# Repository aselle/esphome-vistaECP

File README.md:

# Honeywell/Ademco Vista ECP ESPHome custom component and library

## This fork provides a PCB

This is based on work that was discussed on the main fork issues at 
https://github.com/Dilbert66/esphome-vistaECP/issues/49

Based on the work of the main fork, I created a design and pcb. At the time, the main fork did not provide a fully isolated schematic, which I wanted if I was going to use this on my system.  I invetsigated several designs and settled on this one for my uses. The issue describes a lot of the possibilites. In the end, I used 3 optocouplers and 2 transistors.
You should be able to get the board manufactured cheaply e.g. on JLCPCB.

This is provided with no warranty implied or explicit. I can not be held responsible for you using this work. While, I have tested this in my own equipment for over a year, I suspect the main fork is better tested, so I would recommend this approach only for advanced users who know how to use an oscilloscope.
 
* circuit/v1-manufacture-files
  * has gerber, pdf schematic and case stl files
* circuit/kicad
  * KiCad source for the pcb.

Here's the isolated schematic

Here is what the manufactured product looks like

## Main fork documentation

This is an implementation of an ESPHOME custom component and ESP Library to interface directly to a Safewatch/Honeywell/Ademco Vista 15/20 alarm system using the ECP interface and very inexpensive ESP8266/ESP32 modules .  The ECP library code is based on the arduino source code from Mark Kimsal's repository located at  https://github.com/TANC-security/keypad-firmware.  It has been  completely rewritten as a class and adapted to work on the ESP8266/ESP32 platform using interrupt driven communications and pulse timing. A custom modified version of Peter Lerup's ESPsoftwareserial library (https://github.com/plerup/espsoftwareserial) was also used for the serial communications to work more efficiently within the tight timing of the ESP8266 interrupt window. 

To compensate for the limitations of the minimal zone data sent by the panel, a time to live (TTL) attribute for each faulted zone was used.  The panel only sends fault messages when a zone is faulted or alarmed and does not send data when the zone is restored, therefore the TTL timer is used to reset a zone after a preset duration once it stops receiving those fault/alarm messages for that zone.  You can tweak the TTL setting in the YAML.  The default timer is set to 30 seconds.  I've also added persistent storage and recovery for zone status in the event of a power failure or reboot of the ESP.  The system will use persistent storage to recover the last known status of the zone on restart.

From documented info, it seems that some panels send an F2 command with extra system details but the panel I have here (Vista 20P version 3.xx ADT version) does not.  Only the F7 is available for zone and system status in my case but this is good enough for this purpose. 

As far as writing on the bus and the request to send pulsing sequence, most documentation only discusses keypad traffic and this only uses the the 3rd pulse.  In actuality the pulses are used as noted below depending on the device type requesting to send:
```
Panel pulse 1. Addresses 1-7, expander board (07), etc
Panel pulse 2. Addresses 8-15 - zone expanders, relay modules
Panel pulse 3. Addresses 16-23 - keypads
```
For example, a zone expander that has the address 07, will send it's address on the first pulse only and will send nothing for the 2nd and 3rd pulse.  A keypad with address 16, will send a 1 bit pulse for pulse1 and pulse2 and then it's encoded address on pulse 3. This info was determined from analysis using a zone expander board and Pulseview to monitor the bus. 

If you are not familiar with ESPHome , I suggest you read up on this application at https://esphome.io and home assistant at https://www.home-assistant.io/.   The library class itself can be used outside of the esphome and home assistant systems.  Just use the code as is without the vistalalarm.yaml and vistaalarm.h files and call it's functions within your own application.  

To use this software you simply place the vistaAlarm.yaml file in your main esphome directory, then copy the *.h and *.cpp files from the vistaEcpInterface directory to a similarly named subdirectory (case sensitive) in your esphome main directory and then compile the yaml as usual. The directory name is in the "includes:" option of the yaml.

##### Notes: 
* If you use the zone expanders and/or LRR functions, you might need to clear CHECK messages for the LRR and expanded zones from the panel on boot or restart by entering your access code followed by 1 twice. eg 12341 12341 where 1234 is your access code.

The yaml attributes should be fairly self explanatory for customization. The yaml example also shows how to setup named zones. 

## Features:

* Full zone expander emulation (4219/4229) which will give you  an additional 8 zones to the system per emulated expander plus associated relay outputs. Currently the library will provide emulation for 2 boards for a total of 16 additionals zones. You can even use free pins on the chip as triggers for those zones as well. 

* Relay module emulation. (4204). The system can support 4 module addresses for a total of 16 relay channels. 

* Long Range Radio (LRR) emulation (or monitoring) statuses for more detailed status messages

* Zone status - Open, Busy, Alarmed and Closed with named zones

* Arm, disarm or send any sequence of commands to the panel

* Status indicators - fire, alarm, trouble, armed stay, armed away, instant armed, armed night,  ready, AC status, bypass status, chime status,battery status, check status, zone and relay channel status fields.

* Optional ability to monitor other devices on the bus such as keypads, other expanders, relay boards, RF devices, etc. This requires the #define MONITORTX to be uncommented in vista.h as well as the addition of two resistors (R4 and R5) to the circuit as shown in the schematic.   This adds another serial interrupt routine that captures and decodes all data on the green tx line.  If enabled this data will be used to update zone statuses for external modules.

The following services are published to home assistant for use in various scripts. 

	alarm_disarm: Disarms the alarm with the user code provided, or the code specified in the configuration.
	alarm_arm_home: Arms the alarm in home mode.
	alarm_arm_away: Arms the alarm in away mode.
	alarm_arm_night: Arms the alarm in night mode (no entry delay).
	alarm_trigger_panic: Trigger a panic alarm.
        alarm_trigger_fire: Trigger a fire alarm.
	alarm_keypress: Sends a string of characters to the alarm system. 

## Example in Home Assistant

The returned statuses for Home Assistant are: armed_away, armed_home, armed_night, pending, disarmed,triggered and unavailable.  

Sample Home Assistant Template Alarm Control Panel configuration with simple services (defaults to partition 1):

```
alarm_control_panel:
  - platform: template
    panels:
      safe_alarm_panel:
        name: "Alarm Panel"
        value_template: "{{states('sensor.vistaalarm_system_status')}}"
        code_arm_required: false
        
        arm_away:
          - service: esphome.vistaalarm_alarm_arm_away
                  
        arm_home:
          - service: esphome.vistaalarm_alarm_arm_home
          
        arm_night:
          - service: esphome.vistaalarm_alarm_arm_night
            data_template:
              code: '{{code}}' #if you didnt set it in the yaml, then send the code herefschema
          
        disarm:
          - service: esphome.vistaalarm_alarm_disarm
            data_template:
              code: '{{code}}'                    
```

## Services

- Basic alarm services. These services default to partition 1:

	- "alarm_disarm", Parameter: "code" (access code)
	- "alarm_arm_home" 
	- "alarm_arm_night", Parameter: "code" (access code)
	- "alarm_arm_away"
	- "alarm_trigger_panic"
	- "alarm_trigger_fire"

- Intermediate command service. Use this service if you need more versatility such as setting alarm states on any partition:

	- "set_alarm_state",  Parameters: "partition","state","code"  where partition is the partition number from 1 to 8, state is one of "D" (disarm), "A" (arm_away), "S" (arm_home), "N" (arm_night), "P" (panic) or "F" (fire) and "code" is your panel access code (can be empty for arming, panic and fire cmds )

- Generic command service. Use this service for more complex control:

	- "alarm_keypress",  Parameter: "keys" where keys can be any sequence of keys accepted by your panel. For example to arm in night mode you set keys to be "xxxx33" where xxxx is your access code. 
    
    - "set_zone_fault",Parameters: "zone","fault" where zone is a zone from 9 - 48 and fault is 0 or 1 (0=ok, 1=open)
       The zone number will depend on what your expander address is set to.

## Wiring

### Non-isolated simple version

### Alternative version using transistors instead of an optocoupler for transmit

### Ground Isolated version

## Wiring Notes

* Optocouplers should have a minimum CTR of 50. Recommendations are the 4N35 or TLP521. You can vary the resistor values for the simple version but keep the ratio similar for the voltage dividers R2/R3 and R4/R5. R1 should not be set below 150 ohm. Resistor values are chosen to minimize load on ECP bus while still providing full output signals on the optocouplers. 
* My goal was to keep the design as simple as possible without causing any bus load or interference with maximum signal fidelity.  Since the transmit circuit required high side switching I opted to use an optocoupler since I had a few on hand and it simplified the amount of components needed but proved to have it's own issues as far as CTR requirements.  For those that would prefer not using optocouplers due to availability or other reasons, i've provided a version using transistors for the transmit circuit instead.  

## OTA updates
In order to make OTA updates, connection switch in frontend should be switched to OFF since the  ECP library is using interrupts.

## MQTT with HomeAssistant
If your preference is to use MQTT instead of ESPHOME, you can use the Arduino sketch from the MQTT-Example directory. It supports pretty much all functions of the ESPHOME implementation.  To use, edit the configuration items at the top of the file for your setup then simply put the ino and all *.h and *.cpp vista library files (from directory /src/vistaEcpInterface) in the same sketch directory and compile.  Read the comments within the sketch for more details.   The sketch also supports ArduinoOTA (https://www.arduino.cc/reference/en/libraries/arduinoota/) that will enable you to update the code via wifi once the initial upload is done.  

## Custom Alarm Panel Card

I've added a sample lovelace alarm-panel card copied from the repository at https://github.com/GalaxyGateway/HA-Cards. I've customized it to work with this ESP library's services.   I've also added two new text fields that will be used by the card to display the panel prompts the same way a real keypad does. To configure the card, just place the alarm-panel-card.js file into the /config/www directory of your homeassistant installation and add a new resource in your lovelace configuration pointing to /local/alarm-panel-card.js.  You can then configure the card as shown below. Just substitute your service name to your application.

```
type: 'custom:alarm-keypad-card'
title: Vista_ESPHOME
unique_id: vista1
disp_line1: sensor.vistaalarm_line1
disp_line2: sensor.vistaalarm_line2
scale: 1
service_type: esphome
service: vistaalarm_alarm_keypress
status_A: AWAY
status_B: STAY
status_C: READY
status_D: BYPASS
status_E: TROUBLE
status_F: ''
status_G: ''
status_H: ''
sensor_A: binary_sensor.vistaalarm_away
sensor_B: binary_sensor.vistaalarm_stay
sensor_C: binary_sensor.vistaalarm_ready
sensor_D: binary_sensor.vistaalarm_bypass
sensor_E: binary_sensor.vistaalarm_trouble
button_A: STAY
button_B: AWAY
button_C: DISARM
button_D: BYPASS
button_F: <
button_G: '>'
button_E: ' '
button_H: ' '
cmd_A:
  keys: '12343'
cmd_B:
  keys: '12342'
cmd_C:
  keys: '12341'
cmd_D:
  keys: '12346#'
cmd_E:
  keys: ''
cmd_H:
  keys: ''
cmd_F:
  keys: <
cmd_G:
  keys: '>'
key_0:
  keys: '0'
key_1:
  keys: '1'
key_2:
  keys: '2'
key_3:
  keys: '3'
key_4:
  keys: '4'
key_5:
  keys: '5'
key_6:
  keys: '6'
key_7:
  keys: '7'
key_8:
  keys: '8'
key_9:
  keys: '9'
key_star:
  keys: '*'
key_pound:
  keys: '#'
key_right:
  keys: '>'
key_left:
  keys: <
beep: sensor.vistaalarm_beeps
view_pad: true
view_display: true
view_status: true
view_status_2: true
view_bottom: true

type: 'custom:alarm-keypad-card'
title: Vista_MQTT
unique_id: vista2
disp_line1: sensor.displayline1
disp_line2: sensor.displayline2
scale: 1
service_type: mqtt
service: publish
status_A: AWAY
status_B: STAY
status_C: READY
status_E: BYPASS
status_D: TROUBLE
status_F: ''
status_G: ''
status_H: ''
sensor_A: sensor.vistaaway
sensor_B: sensor.vistastay
sensor_C: sensor.vistaready
sensor_E: sensor.vistabypass
sensor_D: sensor.vistatrouble
button_A: STAY
button_B: AWAY
button_C: DISARM
button_D: BYPASS
cmd_A:
  topic: vista/Set/Cmd
  payload: '!12343'
cmd_B:
  topic: vista/Set/Cmd
  payload: '!12342'
cmd_C:
  topic: vista/Set/Cmd
  payload: '!12341'
cmd_D:
  topic: vista/Set/Cmd
  payload: '!12346#'
key_0:
  topic: vista/Set/Cmd
  payload: '!0'
key_1:
  topic: vista/Set/Cmd
  payload: '!1'
key_2:
  topic: vista/Set/Cmd
  payload: '!2'
key_3:
  topic: vista/Set/Cmd
  payload: '!3'
key_4:
  topic: vista/Set/Cmd
  payload: '!4'
key_5:
  topic: vista/Set/Cmd
  payload: '!5'
key_6:
  topic: vista/Set/Cmd
  payload: '!6'
key_7:
  topic: vista/Set/Cmd
  payload: '!7'
key_8:
  topic: vista/Set/Cmd
  payload: '!8'
key_9:
  topic: vista/Set/Cmd
  payload: '!9'
key_star:
  topic: vista/Set/Cmd
  payload: '!*'
key_pound:
  topic: vista/Set/Cmd
  payload: '!#'
view_pad: true
view_display: true
view_status: true
view_status_2: true
view_bottom: false
beep: sensor.vistabeeps

```

### sample sensor configuration for card using mqtt
```

sensor:

  - platform: mqtt
    state_topic: "vista/Get/DisplayLine/1"
    name: "DisplayLine1"

  - platform: mqtt
    state_topic: "vista/Get/DisplayLine/2"
    name: "DisplayLine2"

  - platform: mqtt
    state_topic: "vista/Get/Status/AWAY"
    name: "vistaaway"
    
  - platform: mqtt
    state_topic: "vista/Get/Status/STAY"
    name: "vistastay"
  
  - platform: mqtt
    state_topic: "vista/Get/Status/READY"
    name: "vistaready"

  - platform: mqtt
    state_topic: "vista/Get/Status/TROUBLE"
    name: "vistatrouble"

  - platform: mqtt
    state_topic: "vista/Get/Status/BYPASS"
    name: "vistabypass"
    
  - platform: mqtt
    state_topic: "vista/Get/Status/CHIME"
    name: "vistachime"    

```

## References 
You can checkout the links below for further reading and other implementation examples. Some portions of the code in the repositories below was used in creating the library.
* https://github.com/TANC-security/keypad-firmware
* https://github.com/cweemin/espAdemcoECP
* https://github.com/TomVickers/Arduino2keypad/

This project is licensed under the Lesser General Public License version 2.1, or (at your option) any later version as per it's use of other libraries and code. Please see COPYING.LESSER for more informatio

## Disclaimer

THIS HARDWARE AND SOFTWARE IS PROVIDED BY THE COPYRIGHT HOLDERS AND CONTRIBUTORS “AS IS” AND ANY EXPRESS OR IMPLIED WARRANTIES, INCLUDING, BUT NOT LIMITED TO, THE IMPLIED WARRANTIES OF MERCHANTABILITY AND FITNESS FOR A PARTICULAR PURPOSE ARE DISCLAIMED. IN NO EVENT SHALL THE COPYRIGHT OWNER OR CONTRIBUTORS BE LIABLE FOR ANY DIRECT, INDIRECT, INCIDENTAL, SPECIAL, EXEMPLARY, OR CONSEQUENTIAL DAMAGES (INCLUDING, BUT NOT LIMITED TO, PROCUREMENT OF SUBSTITUTE GOODS OR SERVICES; LOSS OF USE, DATA, OR PROFITS; OR BUSINESS INTERRUPTION) HOWEVER CAUSED AND ON ANY THEORY OF LIABILITY, WHETHER IN CONTRACT, STRICT LIABILITY, OR TORT (INCLUDING NEGLIGENCE OR OTHERWISE) ARISING IN ANY WAY OUT OF THE USE OF THIS SOFTWARE, EVEN IF ADVISED OF THE POSSIBILITY OF SUCH DAMAGE.

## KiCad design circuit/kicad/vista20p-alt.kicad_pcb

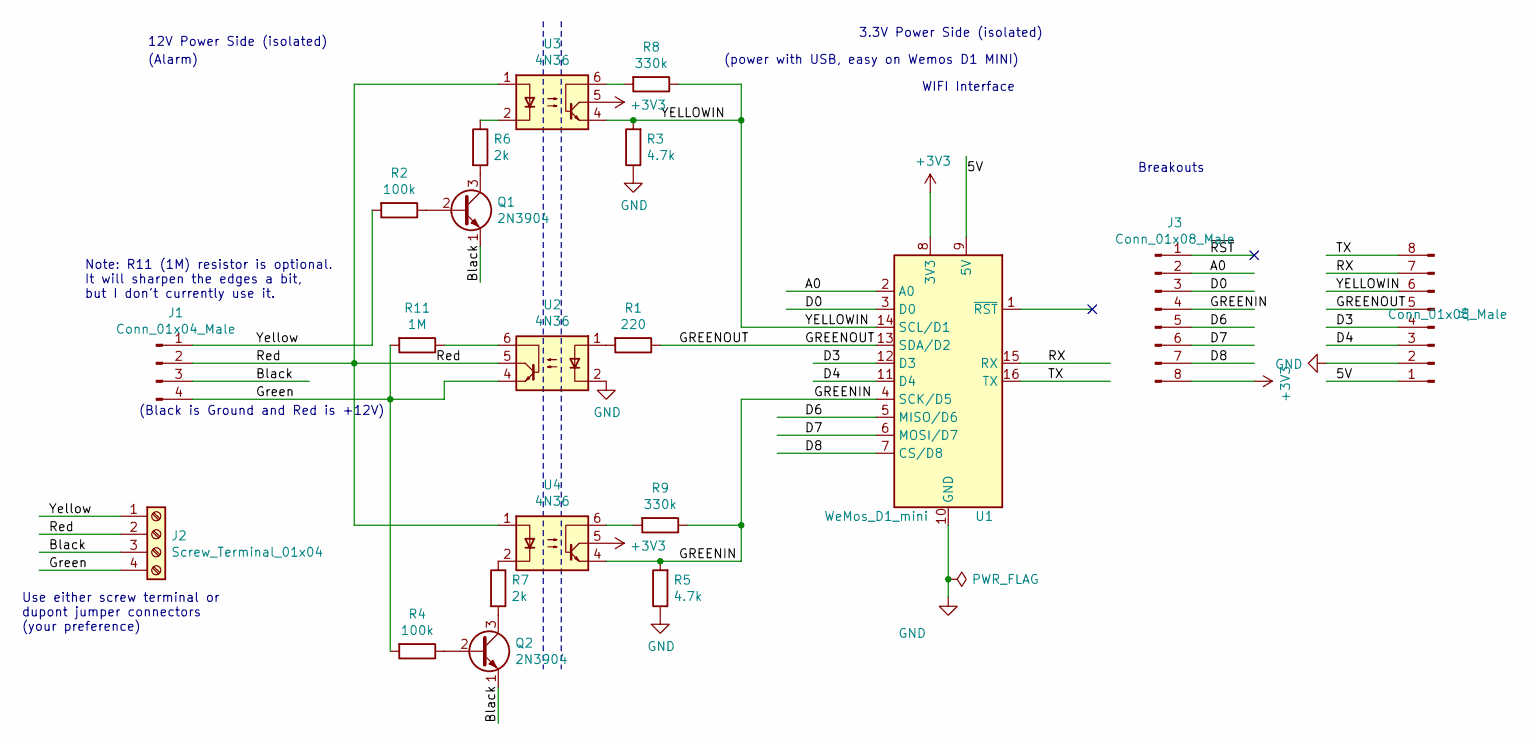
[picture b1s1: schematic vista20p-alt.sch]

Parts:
J1: Conn_01x04_Male; PinHeader_1x04_P2.54mm_Vertical
J2: Screw_Terminal_01x04; TerminalBlock_Phoenix_PT-1,5-4-3.5-H_1x04_P3.50mm_Horizontal
J3, J4: Conn_01x08_Male; PinHeader_1x08_P2.54mm_Vertical
Q1, Q2: 2N3904; TO-92_Inline
R1: 220; R_Axial_DIN0207_L6.3mm_D2.5mm_P10.16mm_Horizontal
R2, R4: 100k; R_Axial_DIN0207_L6.3mm_D2.5mm_P10.16mm_Horizontal
R3, R5: 4.7k; R_Axial_DIN0207_L6.3mm_D2.5mm_P10.16mm_Horizontal
R6, R7: 2k; R_Axial_DIN0207_L6.3mm_D2.5mm_P10.16mm_Horizontal
R8, R9: 330k; R_Axial_DIN0207_L6.3mm_D2.5mm_P10.16mm_Horizontal
R11: 1M; R_Axial_DIN0207_L6.3mm_D2.5mm_P10.16mm_Horizontal
U1: WeMos_D1_mini; WEMOS_D1_mini_light
U2, U3, U4: 4N36; DIP-6_W7.62mm

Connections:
+3V3: J3.8, U1.8 (3V3), U3.5, U4.5
/5V: J4.1, U1.9 (5V)
/A0: J3.2, U1.2 (A0)
/Black: J1.3, J2.3, Q1.1 (E), Q2.1 (E)
/D0: J3.3, U1.3 (D0)
/D3: J4.4, U1.12 (D3)
/D4: J4.3, U1.11 (D4)
/D6: J3.5, U1.5 (MISO/D6)
/D7: J3.6, U1.6 (MOSI/D7)
/D8: J3.7, U1.7 (CS/D8)
/GREENIN: J3.4, R5.2, R9.1, U1.4 (SCK/D5), U4.4
/GREENOUT: J4.5, R1.1, U1.13 (SDA/D2)
/Green: J1.4, J2.4, R4.2, R11.2, U2.4
/RX: J4.7, U1.15 (RX)
/Red: J1.2, J2.2, U2.5, U3.1, U4.1
/TX: J4.8, U1.16 (TX)
/YELLOWIN: J4.6, R3.2, R8.1, U1.14 (SCL/D1), U3.4
/Yellow: J1.1, J2.1, R2.2
/~RST: J3.1, U1.1 (~RST)
GND: J4.2, R3.1, R5.1, U1.10 (GND), U2.2
unnamed: Q1.2 (B), R2.1
unnamed: Q1.3 (C), R6.2
unnamed: Q2.2 (B), R4.1
unnamed: Q2.3 (C), R7.2
unnamed: R1.2, U2.1
unnamed: R6.1, U3.2
unnamed: R7.1, U4.2
unnamed: R8.2, U3.6
unnamed: R9.2, U4.6
unnamed: R11.1, U2.6

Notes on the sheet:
Use either screw terminal or dupont jumper connectors (your preference)
(power with USB, easy on Wemos D1 MINI)
WIFI Interface
(Alarm)
(Black is Ground and Red is +12V)
3.3V Power Side (isolated)
12V Power Side (isolated)
Breakouts
Note: R11 (1M) resistor is optional. It will sharpen the edges a bit, but I don't currently use it.

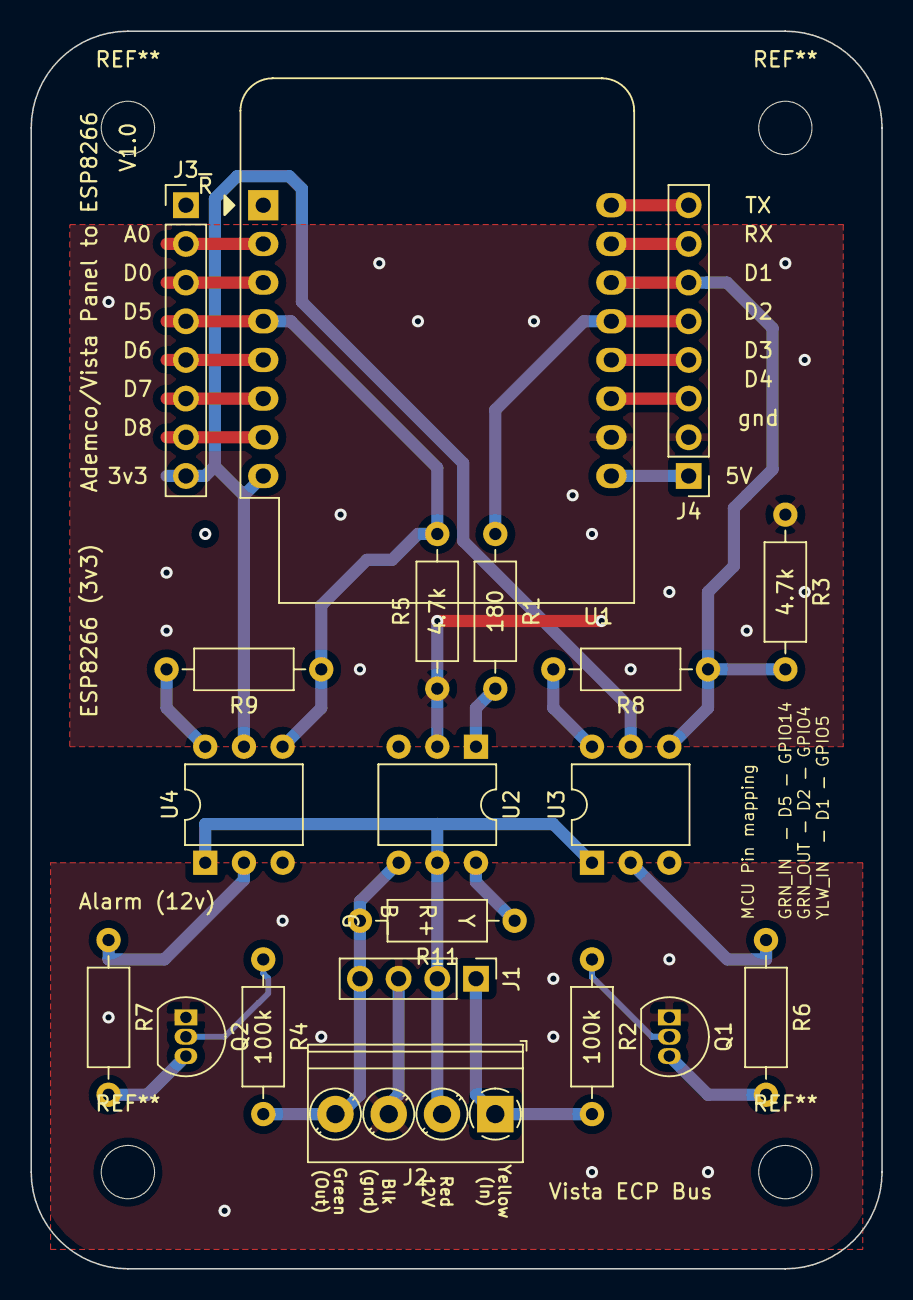
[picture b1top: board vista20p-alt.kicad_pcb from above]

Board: 2 copper layers, 55.9 x 81.3 mm, 20 parts (0 on the bottom side), 30 nets.

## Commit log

2021-10-09 Name zones
2021-10-09 Add parameter for txEnablePin
    This uses existing functionality to drive a pin indicating when any driver of the
    tx output of the microcontroller should be driven. This allows the esp8266 impersonation
    to drive the pin harder when it is transmitting, improving signal integrity.
    This is probably not needed by most users.
2023-02-06 Add pcb, case, and new description
2023-02-08 Remove old gerbers from the kicad directory
